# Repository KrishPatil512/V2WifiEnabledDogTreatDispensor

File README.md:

# Wi-Fi Dog Treat Dispenser V2

A 3D-printed dog treat dispenser controlled from a browser on your local Wi-Fi network. An ESP32 serves a control page and drives a stepper motor that rotates the treat wheel. As the wheel turns, treats fall through the opening in the base.

## Build photos

| Assembled dispenser | Treat wheel and dispensing opening |
| --- | --- |
|  |  |

### ESP32 and TMC2209 carrier PCB

## Design files

[View the assembled dispenser in 3D](cad/ViewableAssemblySTL.STL)

- [SolidWorks assembly](cad/SolidWorks%20Files/Assem.SLDASM) and [part files](cad/SolidWorks%20Files/)
- [STL exports for 3D printing](cad/SolidWorks%20Files/STL/), including the base plate, lower plate, treat hopper, spindexer, and spindexer insert

## ESP32 setup

The ESP32 controls a 1.8° bipolar stepper through a TMC2209 in standalone STEP/DIR mode.

| TMC2209 signal | Connection |
| --- | --- |
| STEP | ESP32 GPIO 25 |
| DIR | ESP32 GPIO 26 |
| EN / ENN (active low) | ESP32 GPIO 27 |
| VIO | ESP32 3.3 V |
| GND | Common ground with the ESP32 and motor supply |
| MS1 and MS2 | Both LOW for 1/8 microstepping |

Connect the motor coils to the driver's two output pairs and power the driver from a separate motor supply. Set the current limit using the procedure for your TMC2209 module and the motor's phase-current rating. [TMC2209 datasheet](https://www.analog.com/media/en/technical-documentation/data-sheets/tmc2209_datasheet_rev1.09.pdf)

1. Open the [Arduino sketch](software/WebServerForDogTreatDispensor/WebServerForDogTreatDispensor.ino) in the Arduino IDE and select your ESP32 board.
2. Set `ssid` and `password` in your local copy of the sketch, then upload it to the ESP32.
3. Open the Serial Monitor at `115200` baud and note the IP address printed when the ESP32 connects to Wi-Fi.
4. From a device on the same network, open `http://<ESP32-IP>` and press **Dispense** to rotate the wheel 45° clockwise. The page also offers quarter turns and full turns in either direction.

## Through-hole PCB

Open the [KiCad project](pcb/DogTreatDispensorPCB/DogTreatDispensorPCB.kicad_pro) for the 76 × 59 mm carrier. It uses 2.54 mm socket strips for the 38-pin ESP32-DevKitC V4 (25.4 mm between rows) and the BIGTREETECH TMC2209 V1.2 (12.7 mm between rows). Match the ESP32 USB connector and the driver's VM and EN pins to the labels on the board. [ESP32 dimensions](https://dl.espressif.com/dl/schematics/esp32_devkitc_v4_dimensions.pdf) · [TMC2209 pinout](https://global.bttwiki.com/TMC2209.html#pinoutfunction)

- Power the ESP32 by USB and connect a 12 V DC motor supply to J1, a 5.08 mm pitch screw terminal.
- Connect the two motor coils to the A1/A2 and B1/B2 pairs on J2, a 3.5 mm pitch screw terminal.
- Fit a 100 µF, 35 V radial capacitor at C1 (8 mm body, 3.5 mm lead pitch) and a 10 kΩ axial resistor at R1 (7.62 mm lead pitch).

## License

[MIT](LICENSE)

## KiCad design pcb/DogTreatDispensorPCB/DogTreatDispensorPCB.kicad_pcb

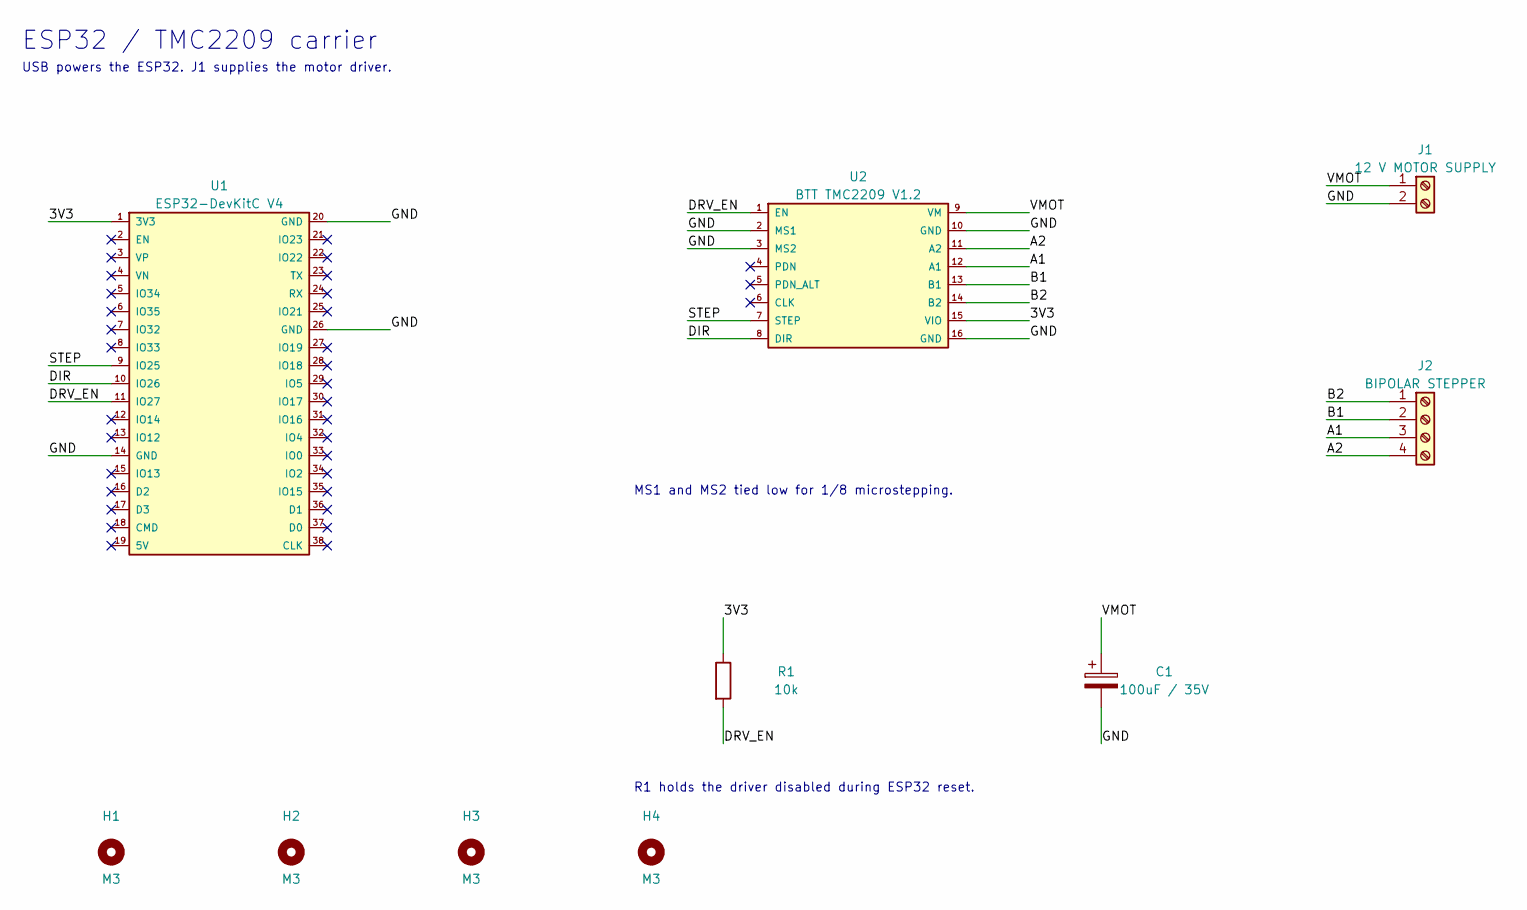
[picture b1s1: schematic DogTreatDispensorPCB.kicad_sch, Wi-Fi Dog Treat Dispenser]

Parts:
C1: 100uF / 35V; CP_Radial_D8.0mm_P3.50mm
H1, H2, H3, H4: M3; MountingHole_3.2mm_M3
J1: 12 V MOTOR SUPPLY; TerminalBlock_Phoenix_MKDS-1,5-2-5.08_1x02_P5.08mm_Horizont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
J2: BIPOLAR STEPPER; TerminalBlock_Phoenix_PT-1,5-4-3.5-H_1x04_P3.50mm_Horizontal
R1: 10k; R_Axial_DIN0207_L6.3mm_D2.5mm_P7.62mm_Horizontal
U1: ESP32-DevKitC V4; ESP32-DevKitC-V4
U2: BTT TMC2209 V1.2; TMC2209-BTT-V1.2

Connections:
/3V3: R1.1, U1.1 (3V3), U2.15 (VIO)
/A1: J2.3 (A1), U2.12 (A1)
/A2: J2.4 (A2), U2.11 (A2)
/B1: J2.2 (B1), U2.13 (B1)
/B2: J2.1 (B2), U2.14 (B2)
/DIR: U1.10 (IO26), U2.8 (DIR)
/DRV_EN: R1.2, U1.11 (IO27), U2.1 (EN)
/GND: C1.2 (-), J1.2 (GND), U1.14 (GND), U1.20 (GND), U1.26 (GND), U2.2 (MS1), U2.3 (MS2), U2.10 (GND), U2.16 (GND)
/STEP: U1.9 (IO25), U2.7 (STEP)
/VMOT: C1.1 (+), J1.1 (VMOT), U2.9 (VM)

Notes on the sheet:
ESP32 / TMC2209 carrier
USB powers the ESP32. J1 supplies the motor driver.
MS1 and MS2 tied low for 1/8 microstepping.
R1 holds the driver disabled during ESP32 reset.

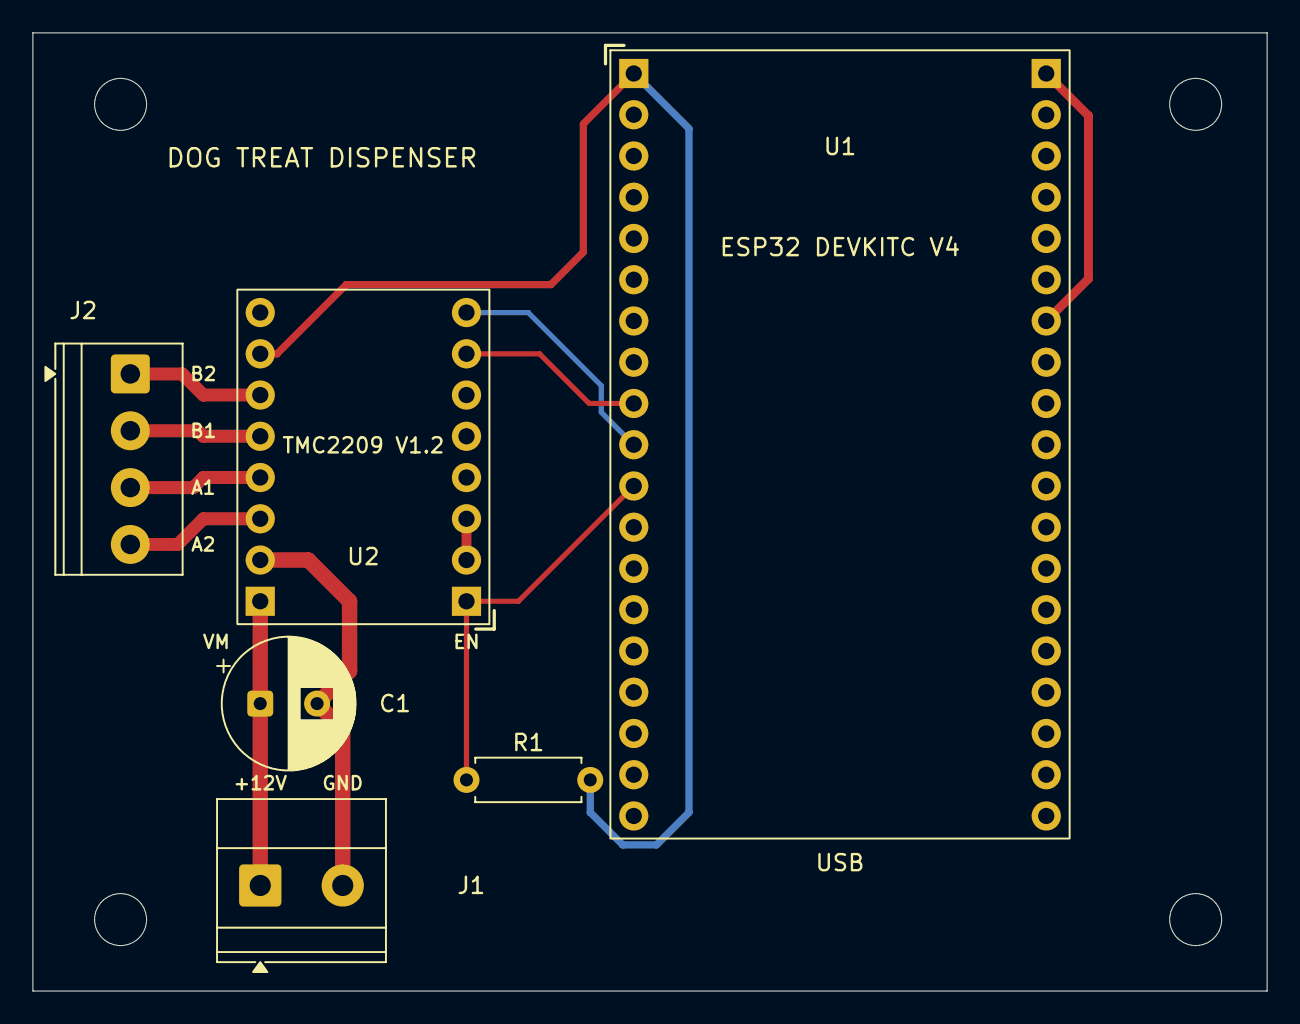
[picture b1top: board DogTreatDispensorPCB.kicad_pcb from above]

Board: 2 copper layers, 76.0 x 59.0 mm, 10 parts (0 on the bottom side), 10 nets.
